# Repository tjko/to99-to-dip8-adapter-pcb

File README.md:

# to99-to-dip8-adapter-pcb
TO-99 to DIP-8 adapter PCB

This is collection of adapters for mounting components in TO-99 package into DIP-8 socket.

This was created to be able to use AD584LH (that is only available in TO-99 package) in place of AD584JN or AD584KN, as AD584LH is higher precision voltage reference and is often being sold for significantly less.

## PCB designs
There is two versions of the PCB:
* Version 1: [KiCad project](/to99-to-pdip8-adapter-v1/)
  
* Version 2: [KiCad project](/to99-to-pdip8-adapter-v2/)

## Kerbers

Ready made kerber files of these two PCBs are found under kerbers/ directory.
These ZIP files are ready to be uploaded to a PCB manufacturer website (such as JLCPCB).

* [Kerber ZIP files](/kerbers/)

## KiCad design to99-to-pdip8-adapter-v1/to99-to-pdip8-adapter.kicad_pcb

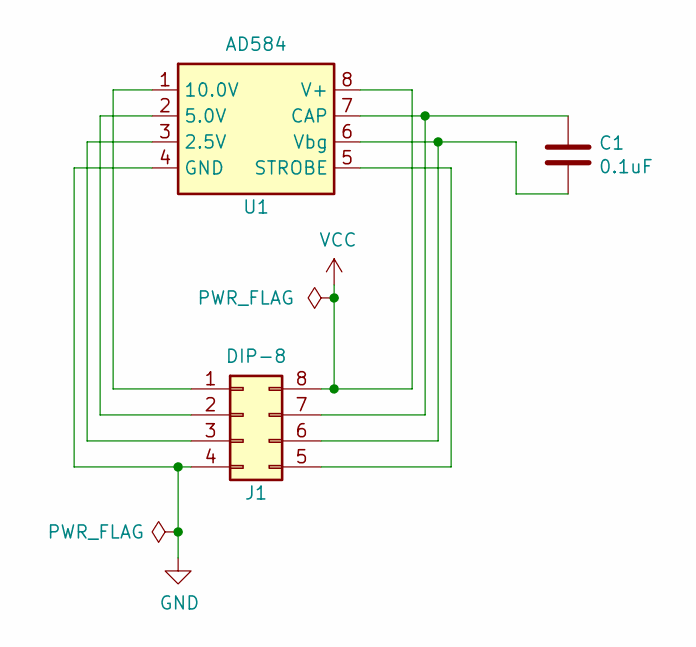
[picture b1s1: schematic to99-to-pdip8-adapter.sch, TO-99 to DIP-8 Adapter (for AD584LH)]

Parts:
C1: 0.1uF; C_0603_1608Metric_Pad1.05x0.95mm_HandSolder
J1: DIP-8; DIP-8_W7.62mm
U1: AD584; TO-99-8_Small

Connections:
GND: J1.4, U1.4 (GND)
unnamed: C1.1, J1.7, U1.7 (CAP)
unnamed: C1.2, J1.6, U1.6 (Vbg)
unnamed: J1.1, U1.1 (10.0V)
unnamed: J1.2, U1.2 (5.0V)
unnamed: J1.3, U1.3 (2.5V)
unnamed: J1.5, U1.5 (STROBE)
VCC: J1.8, U1.8 (V+)

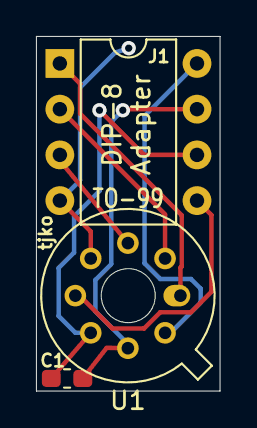
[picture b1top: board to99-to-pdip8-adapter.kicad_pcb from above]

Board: 2 copper layers, 10.2 x 19.7 mm, 3 parts (0 on the bottom side), 8 nets.

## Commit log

2022-01-29 Initial import.
2022-01-29 Added KiCad projects.
2022-01-29 Initial import.
    Added KiCad projects.
    Add photo of finished adapters.
    Author: Timo Kokkonen <tjko@iki.fi>
